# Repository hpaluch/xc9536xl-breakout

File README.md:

Future breakout board for Xilinx XC9536XL-PLC44 CPLD.

WARNING! It is in very early stage!

Made in [Eagle 9.3.0 Free][Eagle 9.3.0 Free]

Used libraries:

- https://www.diymodules.org/download/eagle-libs/usr/0000002221/conv/XILINX.lbr
  - for XC9536 PLC44

[Eagle 9.3.0 Free]: https://www.autodesk.com/products/eagle/free-download

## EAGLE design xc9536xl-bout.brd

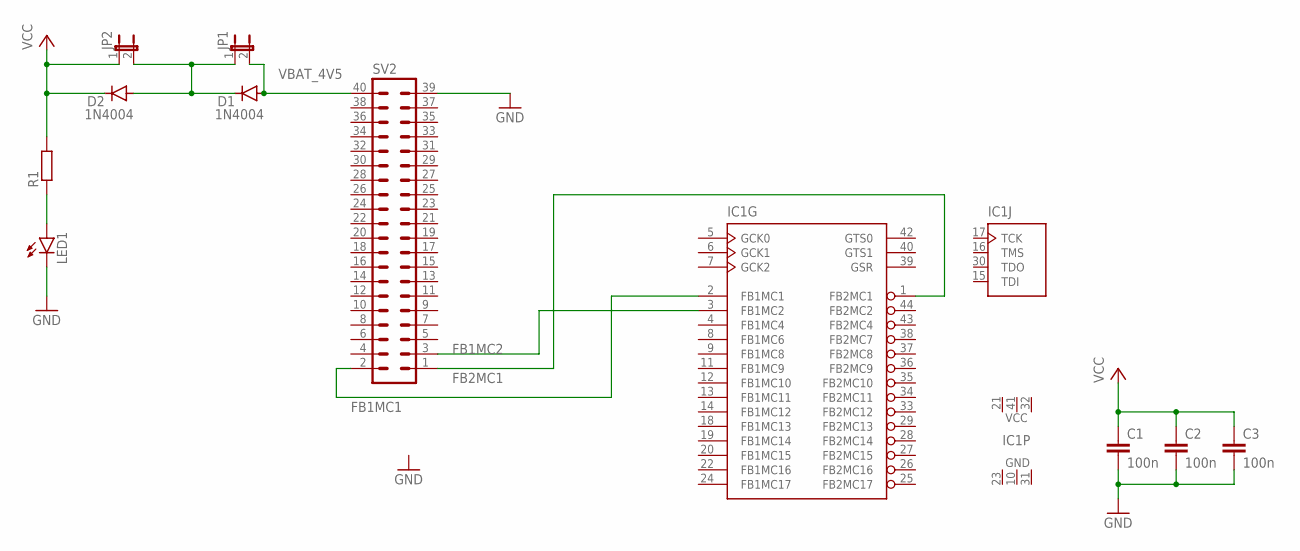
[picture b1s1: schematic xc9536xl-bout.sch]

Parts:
C1, C2, C3: 100n; C050-025X075
D1, D2: 1N4004; DO41-10
IC1: XC9536-44; PLCC-S44
JP1, JP2: JP1E; JP1
LED1: LED5MM
R1: R-EU_0207/10; 0207/10
SV2: ML40

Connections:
FB1MC1: IC1.2 (FB1MC1), SV2.2
FB1MC2: IC1.3 (FB1MC2), SV2.3
FB2MC1: IC1.1 (FB2MC1), SV2.1
GND: C1.2, C2.2, C3.2, IC1.10 (GND), IC1.23 (GND), IC1.31 (GND), LED1.K (C), SV2.39
unnamed: D1.C, D2.A, JP1.1, JP2.2
unnamed: LED1.A, R1.1
VBAT_4V5: D1.A, JP1.2, SV2.40
VCC: C1.1, C2.1, C3.1, D2.C, IC1.21 (VCC), IC1.32 (VCC), IC1.41 (VCC), JP2.1, R1.2

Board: 2 copper layers, 15 parts (0 on the bottom side), 8 nets, no tracks yet.

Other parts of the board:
U$1, U$2, U$3, U$4: DRIL-3,5

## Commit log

2021-01-26 Initial early commit
2021-01-26 Added decoupling capacitors for Xilinx supply pins
2021-01-27 Voltage drop diodes and few signals for tests
